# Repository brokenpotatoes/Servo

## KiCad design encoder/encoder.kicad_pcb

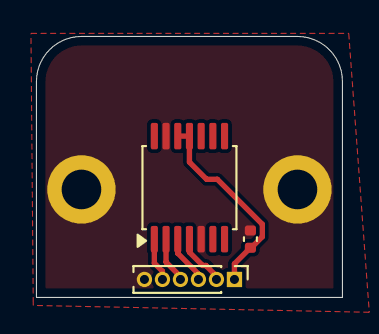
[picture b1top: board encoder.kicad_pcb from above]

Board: 2 copper layers, 17.0 x 14.5 mm, 5 parts (0 on the bottom side), 6 nets.

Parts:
C1: 100nF; C_0402_1005Metric
H1, H2: MountingHole_Pad_MP; MountingHole_2.2mm_M2_DIN965_Pad
J1: Conn_01x06_Pin; PinHeader_1x06_P1.00mm_Vertical
U1: AS5047P; TSSOP-14_4.4x5mm_P0.65mm

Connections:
/ENC_CS: J1.5, U1.1 (~CS)
/MISO: J1.3, U1.3 (MISO)
/MOSI: J1.2, U1.4 (MOSI)
/SCK: J1.4, U1.2 (CLK)
GND: C1.2, H1.1, H2.1, J1.6, U1.5 (TST), U1.13 (GND)
VDD: C1.1, J1.1, U1.11 (VDD), U1.12 (VDD3V3)

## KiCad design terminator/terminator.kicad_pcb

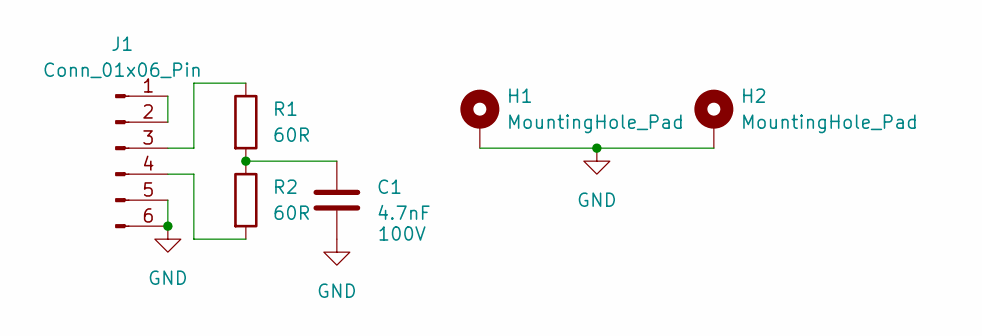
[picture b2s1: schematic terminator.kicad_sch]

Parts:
C1: 4.7nF; C_1206_3216Metric; Voltage Rating 100V; LCSC Part C393168
H1, H2: MountingHole_Pad; MountingHole_2.2mm_M2_Pad
J1: Conn_01x06_Pin; JST_XH_S6B-XH-A_1x06_P2.50mm_Horizontal; LCSC Part C157919
R1, R2: 60R; C_1206_3216Metric; LCSC Part C2086866

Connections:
GND: C1.2, H1.1, H2.1, J1.5, J1.6
unnamed: C1.1, R1.2, R2.1
unnamed: J1.1, J1.2
unnamed: J1.3, R1.1
unnamed: J1.4, R2.2

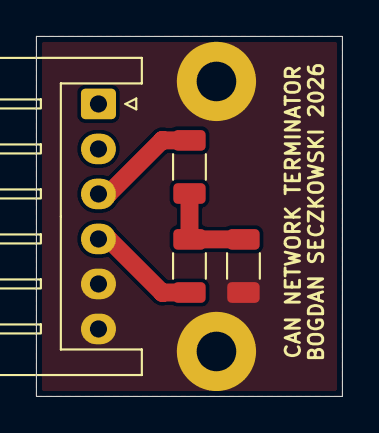
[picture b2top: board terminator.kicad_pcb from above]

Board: 2 copper layers, 17.0 x 20.0 mm, 6 parts (0 on the bottom side), 5 nets.

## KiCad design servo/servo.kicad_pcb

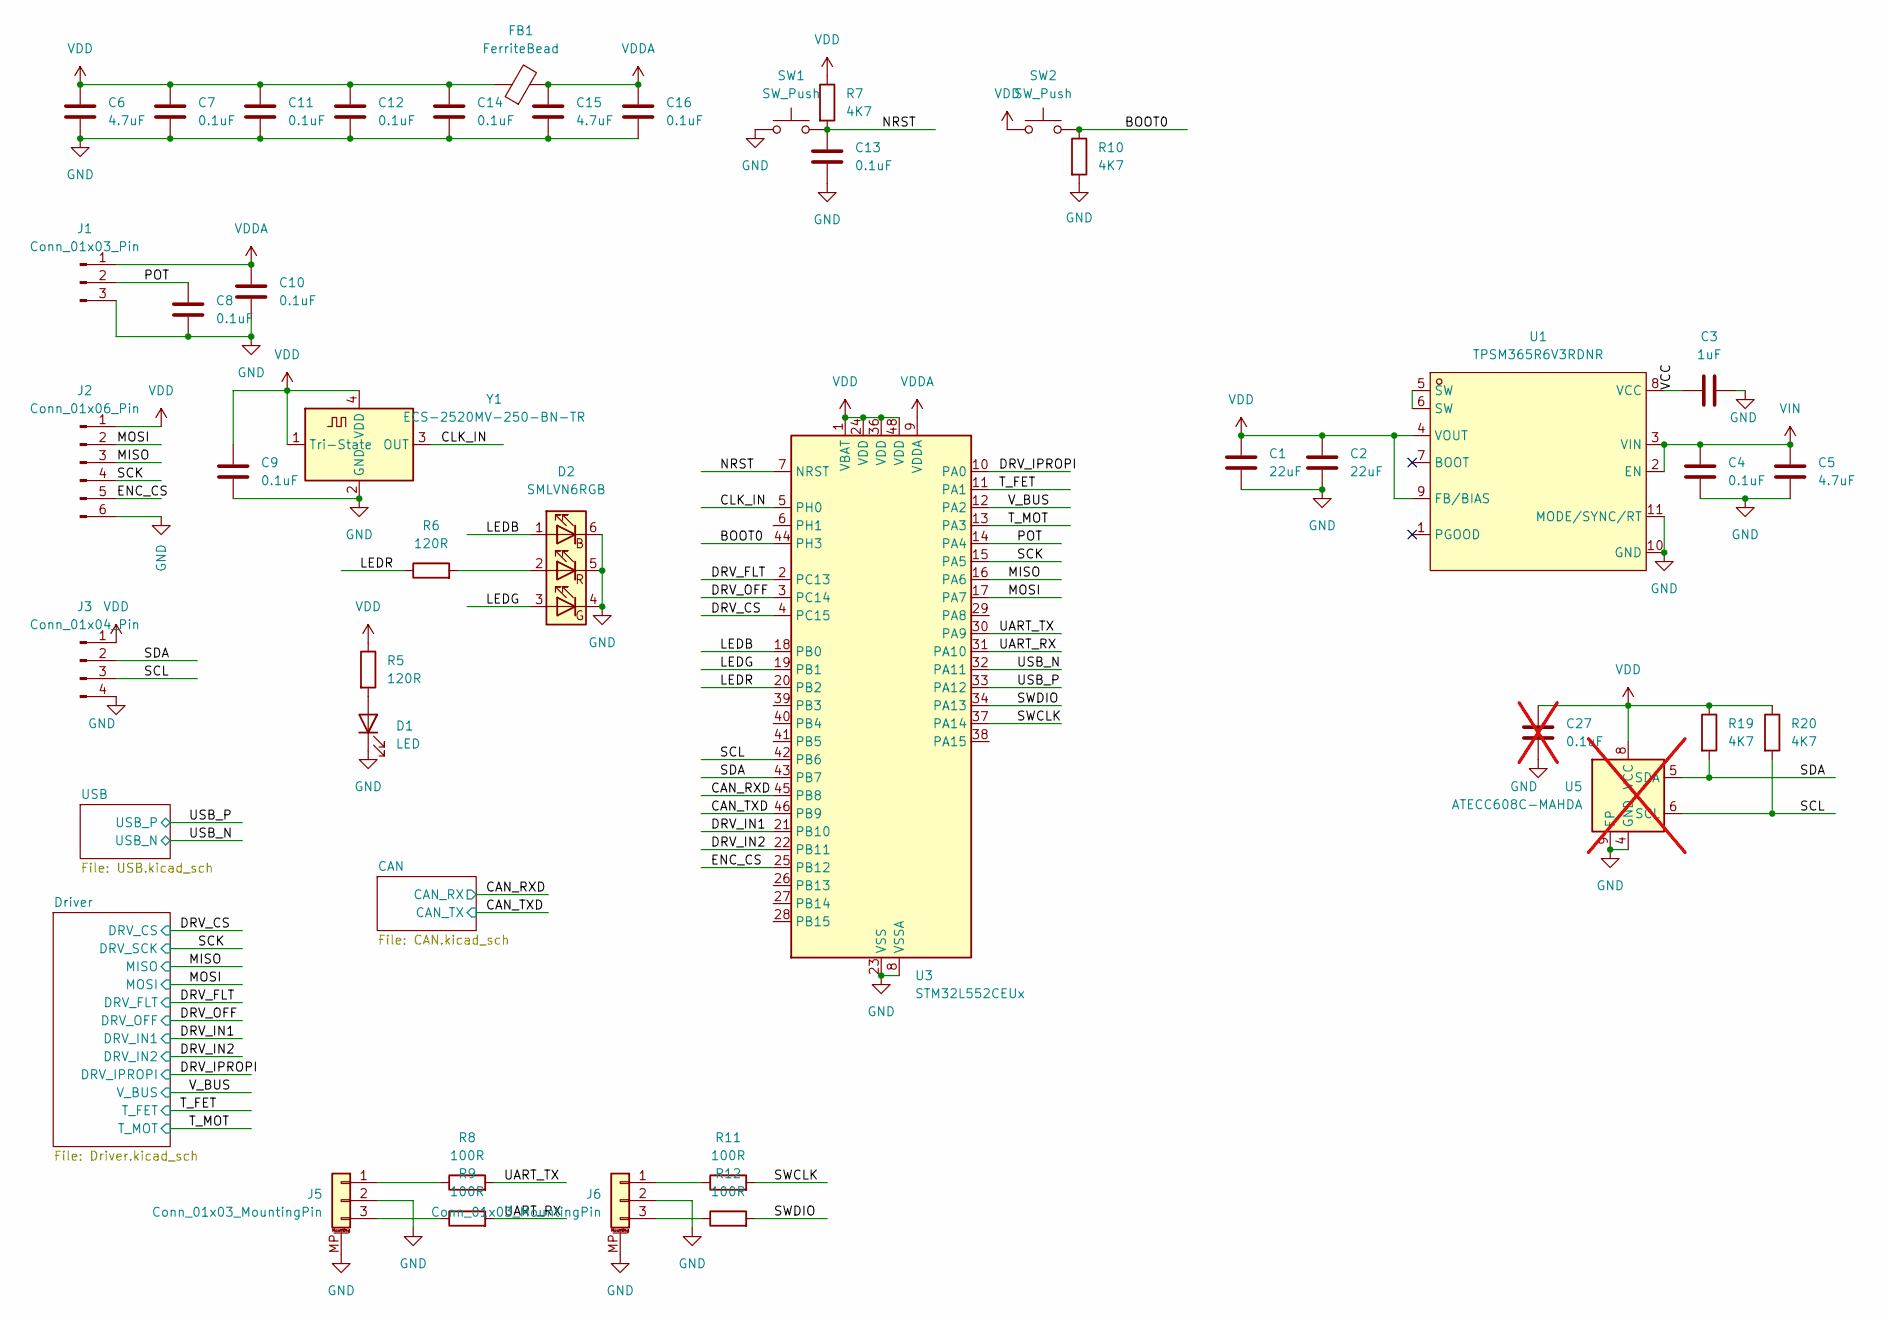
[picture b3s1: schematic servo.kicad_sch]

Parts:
C1, C2: 22uF; C_0402_1005Metric; Voltage Rating 10V; LCSC Part C3845593
C3: 1uF; C_0402_1005Metric; Voltage Rating 16V; LCSC Part C77006
C4: 0.1uF; C_0603_1608Metric; Voltage Rating 100V; LCSC Part C77058
C5: 4.7uF; C_1206_3216Metric; Voltage Rating 100V; LCSC Part C237304
C6, C15: 4.7uF; C_0402_1005Metric; Voltage Rating 16V; LCSC Part C318563
C7, C8, C9, C10, C11, C12, C13, C14, C16: 0.1uF; C_0402_1005Metric; Voltage Rating 16V; LCSC Part C71629
C27: 0.1uF; C_0402_1005Metric; Voltage Rating 16V; LCSC Part C71629; not fitted
D1: LED; LED_0402_1005Metric; LCSC Part C264407
D2: SMLVN6RGB; LED_ROHM_SMLVN6; LCSC Part C2909770
FB1: FerriteBead; L_0402_1005Metric; LCSC Part C88970
J1: Conn_01x03_Pin; PinHeader_1x03_P1.00mm_Vertical
J2: Conn_01x06_Pin; PinHeader_1x06_P1.00mm_Vertical
J3: Conn_01x04_Pin; PinHeader_1x04_P1.00mm_Vertical
J5, J6: Conn_01x03_MountingPin; JST_GH_SM03B-GHS-TB_1x03-1MP_P1.25mm_Horizontal; LCSC Part C514175
R5, R6: 120R; R_0402_1005Metric; LCSC Part C445577
R7, R10, R19, R20: 4K7; R_0402_1005Metric; LCSC Part C400631
R8, R9, R11, R12: 100R; R_0402_1005Metric; LCSC Part C844502
SW1, SW2: SW_Push; SW_SPST_PTS810; LCSC Part C221895
U1: TPSM365R6V3RDNR; QFN-11_L4.5-W3.5-P0.50-TL_TPSM365R6FRDNR; LCSC Part C18208843
U3: STM32L552CEUx; QFN-48-1EP_7x7mm_P0.5mm_EP5.6x5.6mm; LCSC Part C1236634
U5: ATECC608C-MAHDA; DFN-8-1EP_3x2mm_P0.5mm_EP1.3x1.5mm; LCSC Part C23291019; not fitted
Y1: ECS-2520MV-250-BN-TR; Oscillator_SMD_ECS_2520MV-xxx-xx-4Pin_2.5x2.0mm; LCSC Part C405463

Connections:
/BOOT0: R10.1, SW2.2, U3.44 (PH3)
/CAN_RXD: U3.45 (PB8); also elsewhere on the board
/CAN_TXD: U3.46 (PB9); also elsewhere on the board
/CLK_IN: U3.5 (PH0), Y1.3 (OUT)
/DRV_CS: U3.4 (PC15); also elsewhere on the board
/DRV_FLT: U3.2 (PC13); also elsewhere on the board
/DRV_IN1: U3.21 (PB10); also elsewhere on the board
/DRV_IN2: U3.22 (PB11); also elsewhere on the board
/DRV_IPROPI: U3.10 (PA0); also elsewhere on the board
/DRV_OFF: U3.3 (PC14); also elsewhere on the board
/ENC_CS: J2.5, U3.25 (PB12)
/LEDB: D2.1 (BA), U3.18 (PB0)
/LEDG: D2.3 (GA), U3.19 (PB1)
/LEDR: R6.1, U3.20 (PB2)
/MISO: J2.3, U3.16 (PA6); also elsewhere on the board
/MOSI: J2.2, U3.17 (PA7); also elsewhere on the board
/NRST: C13.1, R7.2, SW1.2, U3.7 (NRST)
/POT: C8.1, J1.2, U3.14 (PA4)
/SCK: J2.4, U3.15 (PA5); also elsewhere on the board
/SCL: J3.3, R20.2, U3.42 (PB6), U5.6 (SCL)
/SDA: J3.2, R19.2, U3.43 (PB7), U5.5 (SDA)
/SWCLK: R11.2, U3.37 (PA14)
/SWDIO: R12.2, U3.34 (PA13)
/T_FET: U3.11 (PA1); also elsewhere on the board
/T_MOT: U3.13 (PA3); also elsewhere on the board
/UART_RX: R9.2, U3.31 (PA10)
/UART_TX: R8.2, U3.30 (PA9)
/USB_N: U3.32 (PA11); also elsewhere on the board
/USB_P: U3.33 (PA12); also elsewhere on the board
/VCC: C3.1, U1.8 (VCC)
/V_BUS: U3.12 (PA2); also elsewhere on the board
GND: C1.2, C2.2, C3.2, C4.2, C5.2, C6.2, C7.2, C8.2, C9.2, C10.2, C11.2, C12.2, C13.2, C14.2, C15.2, C16.2, C27.2, D1.1 (K), D2.4 (GK), D2.5 (RK), D2.6 (BK), J1.3, J2.6, J3.4, J5.2, J5.MP (MountPin), J6.2, J6.MP (MountPin), R10.2, SW1.1, U1.10 (GND), U1.11 (MODE/SYNC/RT), U3.8 (VSSA), U3.23 (VSS), U3.35 (VSS), U3.47 (VSS), U3.49 (VSS), U5.4 (GND), U5.9 (EP), Y1.2 (GND); also elsewhere on the board
unnamed: D1.2 (A), R5.2
unnamed: D2.2 (RA), R6.2
unnamed: J5.1, R8.1
unnamed: J5.3, R9.1
unnamed: J6.1, R11.1
unnamed: J6.3, R12.1
unnamed: U1.5 (SW), U1.6 (SW)
VDD: C1.1, C2.1, C6.1, C7.1, C9.1, C11.1, C12.1, C14.1, C27.1, FB1.1, J2.1, J3.1, R5.1, R7.1, R19.1, R20.1, SW2.1, U1.4 (VOUT), U1.9 (FB/BIAS), U3.1 (VBAT), U3.24 (VDD), U3.36 (VDD), U3.48 (VDD), U5.8 (VCC), Y1.1 (Tri-State), Y1.4 (VDD); also elsewhere on the board
VDDA: C10.1, C15.1, C16.1, FB1.2, J1.1, U3.9 (VDDA); also elsewhere on the board
VIN: C4.1, C5.1, U1.2 (EN), U1.3 (VIN); also elsewhere on the board

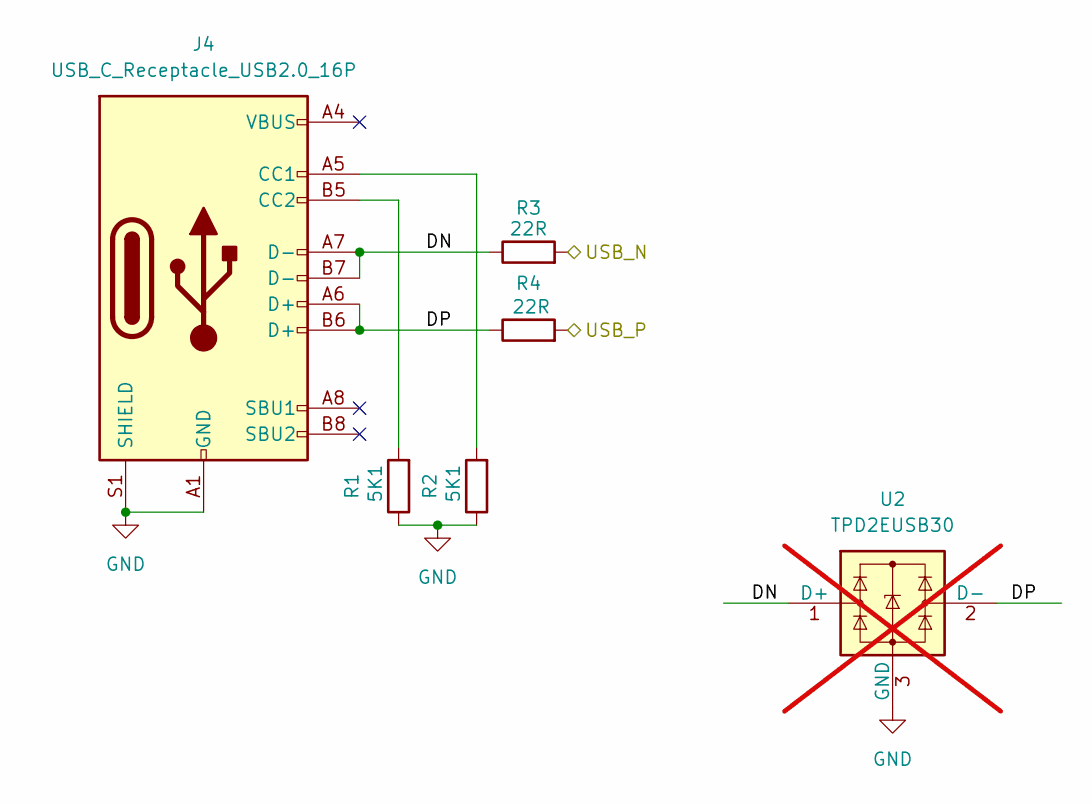
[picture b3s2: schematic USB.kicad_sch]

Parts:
J4: USB_C_Receptacle_USB2.0_16P; USB_C_Receptacle_GCT_USB4105-xx-A_16P_TopMnt_Horizontal; LCSC Part C3020560
R1, R2: 5K1; R_0402_1005Metric; LCSC Part C278598
R3, R4: 22R; R_0402_1005Metric; LCSC Part C482106
U2: TPD2EUSB30; Texas_DRT-3; LCSC Part C94934; not fitted

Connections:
/USB/DN: J4.A7 (D-), J4.B7 (D-), R3.1, U2.1 (D+)
/USB/DP: J4.A6 (D+), J4.B6 (D+), R4.1, U2.2 (D-)
/USB_N: R3.2; also elsewhere on the board
/USB_P: R4.2; also elsewhere on the board
GND: J4.A1 (GND), J4.A12 (GND), J4.B1 (GND), J4.B12 (GND), J4.S1 (SHIELD), R1.1, R2.1, U2.3 (GND); also elsewhere on the board
unnamed: J4.A5 (CC1), R2.2
unnamed: J4.B5 (CC2), R1.2

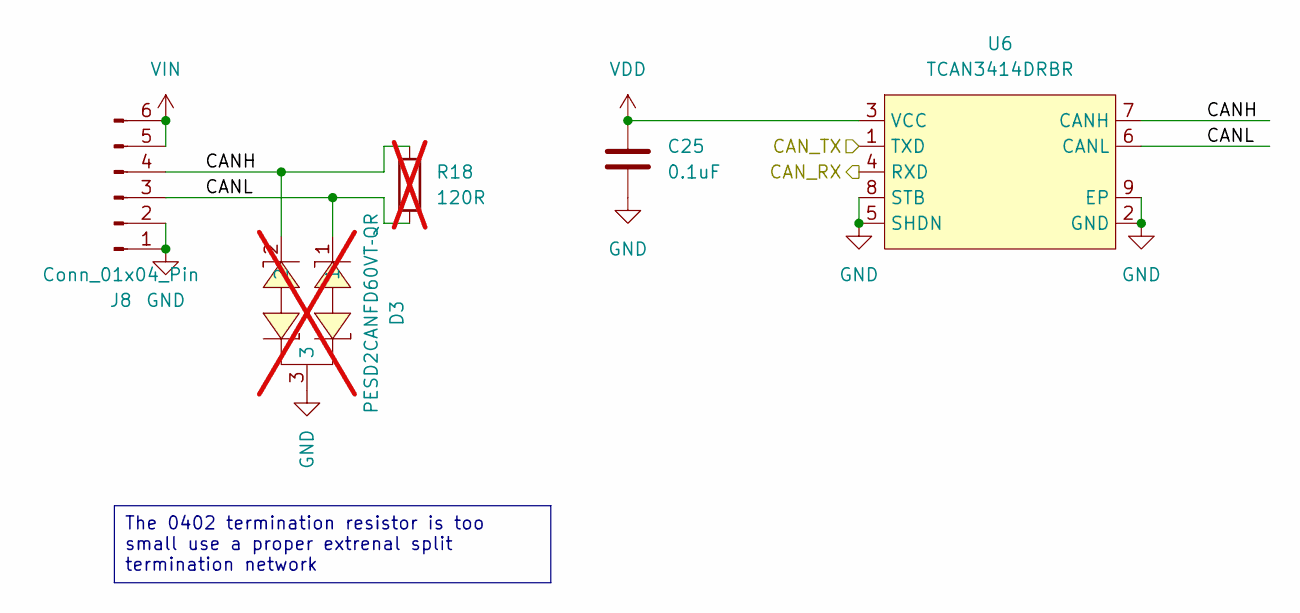
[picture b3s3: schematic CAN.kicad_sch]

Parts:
C25: 0.1uF; C_0402_1005Metric; Voltage Rating 16V; LCSC Part C71629
D3: PESD2CANFD60VT‑QR; SOT-23-3_L2.9-W1.3-P1.90-LS2.4-BL-1; LCSC Part C3711787; not fitted
J8: Conn_01x04_Pin; JST_XH_S6B-XH-A_1x06_P2.50mm_Horizontal; LCSC Part C157919
R18: 120R; R_0402_1005Metric; LCSC Part C445577; not fitted
U6: TCAN3414DRBR; WSON-8_L3.0-W3.0-P0.65-TL-EP; LCSC Part C31542495

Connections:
/CAN/CANH: D3.2, J8.4, R18.2, U6.7 (CANH)
/CAN/CANL: D3.1, J8.3, R18.1, U6.6 (CANL)
/CAN_RXD: U6.4 (RXD); also elsewhere on the board
/CAN_TXD: U6.1 (TXD); also elsewhere on the board
GND: C25.2, D3.3, J8.1, J8.2, U6.2 (GND), U6.5 (SHDN), U6.8 (STB), U6.9 (EP); also elsewhere on the board
VDD: C25.1, U6.3 (VCC); also elsewhere on the board
VIN: J8.5, J8.6; also elsewhere on the board

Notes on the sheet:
The 0402 termination resistor is too small use a proper extrenal split termination network

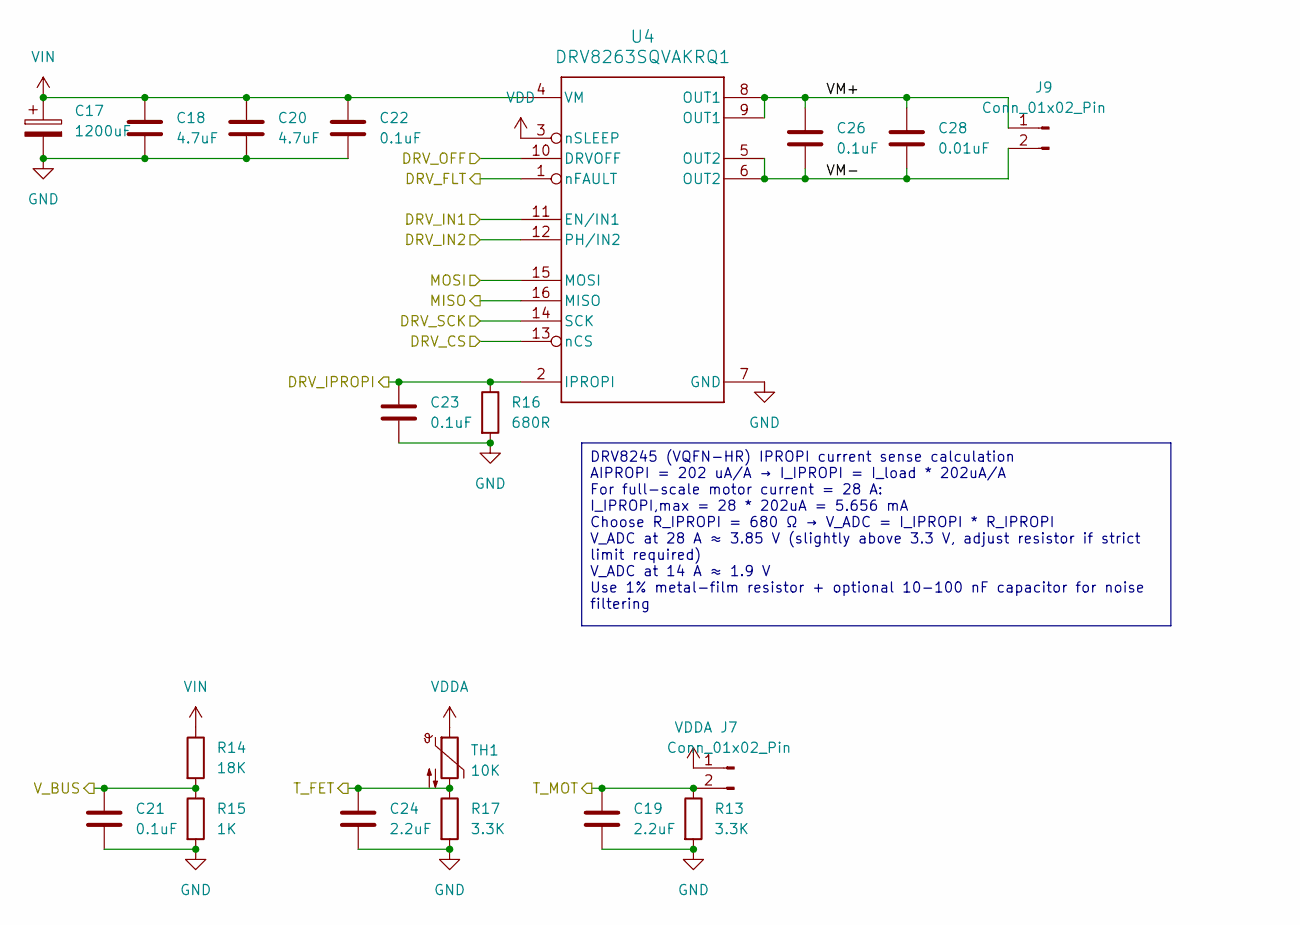
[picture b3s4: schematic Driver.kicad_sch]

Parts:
C17: 1200uF; Rubycon 63ZLJ1200M18X20; Voltage Rating 63V; LCSC Part C700866
C18, C20: 4.7uF; C_1206_3216Metric; Voltage Rating 100V; LCSC Part C237304
C19, C24: 2.2uF; C_0402_1005Metric; Voltage Rating 16V; LCSC Part C170151
C21, C23: 0.1uF; C_0402_1005Metric; Voltage Rating 16V; LCSC Part C71629
C22, C26: 0.1uF; C_0603_1608Metric; Voltage Rating 100V; LCSC Part C77058
C28: 0.01uF; C_0603_1608Metric; Voltage Rating 100V; LCSC Part C161232
J7: Conn_01x02_Pin; PinHeader_1x02_P1.00mm_Vertical; LCSC Part C3000141
J9: Conn_01x02_Pin; Servo
R13, R17: 3.3K; R_0402_1005Metric; LCSC Part C445607
R14: 18K; R_0402_1005Metric; LCSC Part C482065
R15: 1K; R_0402_1005Metric; LCSC Part C242161
R16: 680R; R_0402_1005Metric; LCSC Part C242161
TH1: 10K; R_0402_1005Metric; LCSC Part C209959
U4: DRV8263SQVAKRQ1; RXZ0016A-MFG; LCSC Part C51893863

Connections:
/DRV_CS: U4.13 (nCS); also elsewhere on the board
/DRV_FLT: U4.1 (nFAULT); also elsewhere on the board
/DRV_IN1: U4.11 (EN/IN1); also elsewhere on the board
/DRV_IN2: U4.12 (PH/IN2); also elsewhere on the board
/DRV_IPROPI: C23.1, R16.1, U4.2 (IPROPI); also elsewhere on the board
/DRV_OFF: U4.10 (DRVOFF); also elsewhere on the board
/Driver/VM+: C26.1, C28.1, J9.1, U4.8 (OUT1), U4.9 (OUT1)
/Driver/VM-: C26.2, C28.2, J9.2, U4.5 (OUT2), U4.6 (OUT2)
/MISO: U4.16 (MISO); also elsewhere on the board
/MOSI: U4.15 (MOSI); also elsewhere on the board
/SCK: U4.14 (SCK); also elsewhere on the board
/T_FET: C24.1, R17.1, TH1.2; also elsewhere on the board
/T_MOT: C19.1, J7.2, R13.1; also elsewhere on the board
/V_BUS: C21.1, R14.2, R15.1; also elsewhere on the board
GND: C17.2, C18.2, C19.2, C20.2, C21.2, C22.2, C23.2, C24.2, R13.2, R15.2, R16.2, R17.2, U4.7 (GND); also elsewhere on the board
VDD: U4.3 (nSLEEP); also elsewhere on the board
VDDA: J7.1, TH1.1; also elsewhere on the board
VIN: C17.1, C18.1, C20.1, C22.1, R14.1, U4.4 (VM); also elsewhere on the board

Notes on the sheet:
DRV8245 (VQFN-HR) IPROPI current sense calculation AIPROPI = 202 uA/A → I_IPROPI = I_load * 202uA/A For full-scale motor current = 28 A: I_IPROPI,max = 28 * 202uA = 5.656 mA Choose R_IPROPI = 680 Ω → V_ADC = I_IPROPI * R_IPROPI V_ADC at 28 A ≈ 3.85 V (slightly above 3.3 V, adjust resistor if strict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

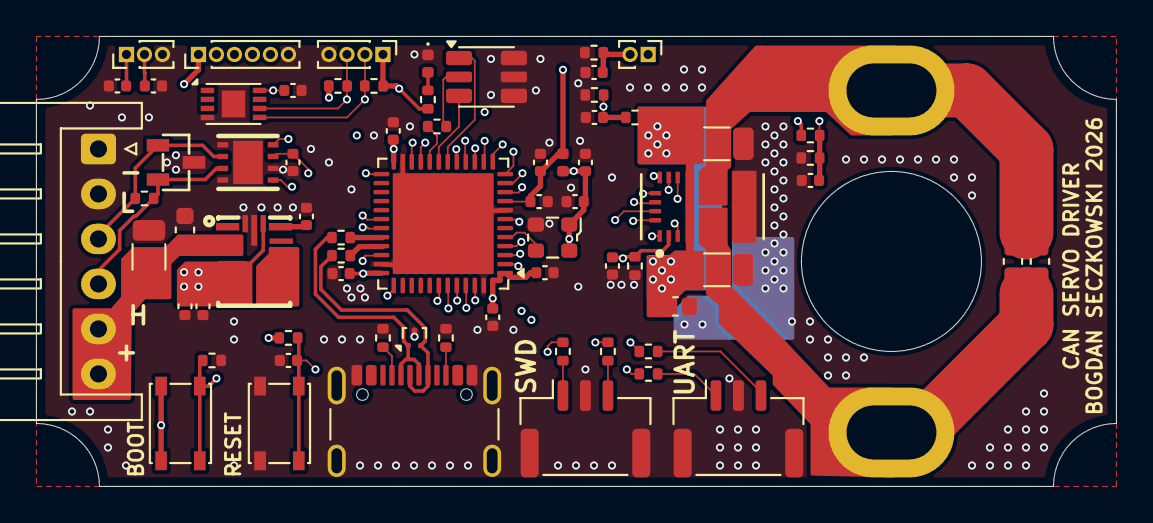
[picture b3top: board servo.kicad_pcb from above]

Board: 6 copper layers, 60.0 x 25.0 mm, 71 parts (1 on the bottom side), 50 nets.

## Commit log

2026-03-01 Initial Upload
2026-03-01 Add BOMs
2026-03-05 Made the encoder PCB
